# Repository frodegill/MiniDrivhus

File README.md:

## about project

Minidrivhus (english: indoor greenhouse) started as a dedicated system for pre-cultivating seeds indoors. It was based on ESP8266 and a custom shield that could support up to 3 soil sensors 3 water pumps and sensors for temperature, humidity and light intensity. There was also a relay for controlling an external grow light, and I've made custom PCBs for small and medium-sized indoor grow lights.  
With all this in place, I also started to make an outdoor greenhouse. When it was completed I expanded the project to also support outdoor greenhouse, which meant I had to add a relay to turn on and off a fan, sensors for outdoor temperature and humidity, a relay for operating a valve controlling water flow to an intermediate water reservoir, sensors for low and high level of water in this reservoir and voltage sensor for the solar panel charged 12V car battery that would power the whole system.  
Unfortunately, the first set of soil sensors did not handle humid/wet environment very well and the second (waterproof) soil sensor had a very limited value range, so I have now started redoing the whole system where the sensors are connected by RS-485 and the water pumps are controlled by a 16-channel multiplexer so one system can control up to 15 plants (having one channel act as an Off channel). To control this I needed more GPIO pins than the ESP8266 provided, so the new system will be based on an ESP32. Stay tuned for new and improved PCBs and source code!

## pictures

The original indoor greenhouse, ready for pre-cultivating seeds:  

Setup for the outdoor greenhouse. 3 systems, each controlling 3 water pumps, for a total of 9 buckets for plants. There is also a small controller for the main water valve and a solar charge controller  

I have 3 x 210 liter buckets for collecting rain water. The water is gravity-fed into an intermediate bucket in a corner of the greenhouse. All water pumps are located in this bucket. There are low- and high water level sensors that are used to control when a water valve is opened and water flows down from the 3 large buckets.  

A complete setup looks like this:  

..and after automatically watering plants all summer, it looks like this:

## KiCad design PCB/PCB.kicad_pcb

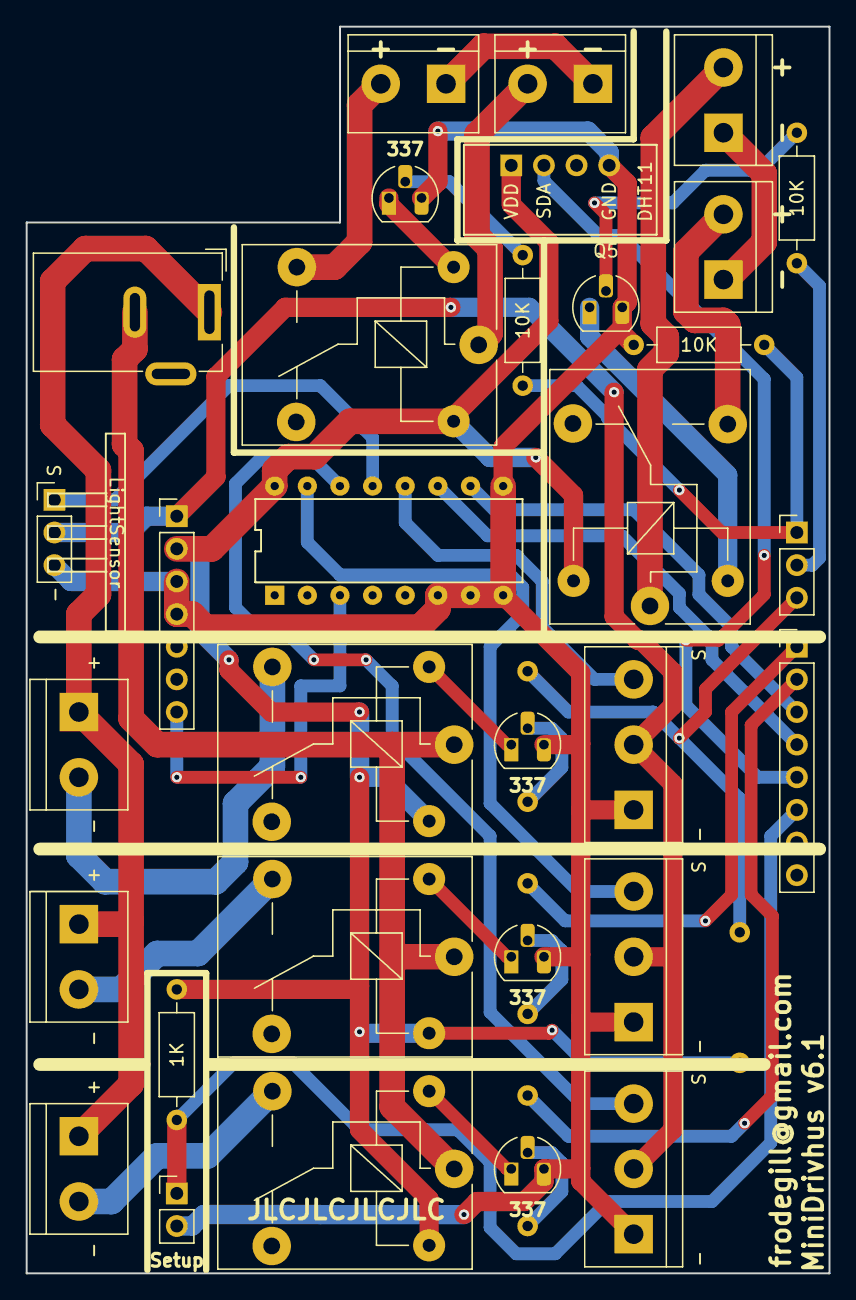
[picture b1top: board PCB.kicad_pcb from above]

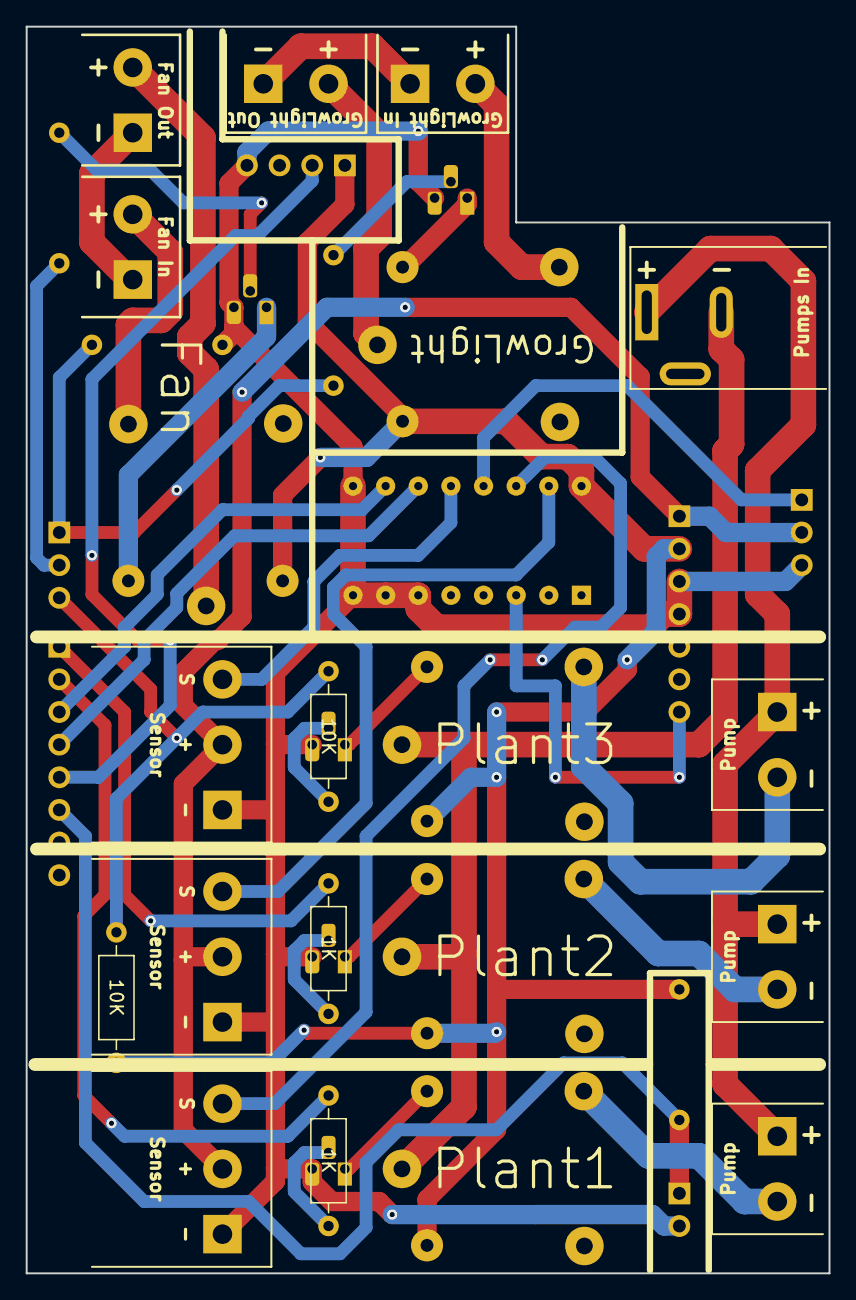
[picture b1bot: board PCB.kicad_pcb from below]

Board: 2 copper layers, 62.5 x 97.0 mm, 36 parts (4 on the bottom side), 38 nets.

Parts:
J1: PWR,A0; PinHeader_1x07_P2.54mm_Vertical
J2: Pump In; BarrelJack_Wuerth_6941xx301002
J3: LightSensor
J4: Pump1; TerminalBlock_bornier-2_P5.08mm
J5: Sensor1; TerminalBlock_bornier-3_P5.08mm
J6: GrowLight In; TerminalBlock_bornier-2_P5.08mm
J7: Pump2; TerminalBlock_bornier-2_P5.08mm
J8: Sensor2; TerminalBlock_bornier-3_P5.08mm
J9: Setup; PinHeader_1x02_P2.54mm_Vertical
J10: D8-D10; PinHeader_1x03_P2.54mm_Vertical
J11: D0-D7; PinHeader_1x08_P2.54mm_Vertical
J12: GrowLight Out; TerminalBlock_bornier-2_P5.08mm
J13: Pump3; TerminalBlock_bornier-2_P5.08mm
J14: Sensor3; TerminalBlock_bornier-3_P5.08mm
J15: Fan In; TerminalBlock_bornier-2_P5.08mm
J16: Fan Out; TerminalBlock_bornier-2_P5.08mm
K1: Relay1; Relay_SPDT_SANYOU_SRD_Series_Form_C
K2: RelayGrowlight; Relay_SPDT_SANYOU_SRD_Series_Form_C
K3: Relay2; Relay_SPDT_SANYOU_SRD_Series_Form_C
K4: Relay3; Relay_SPDT_SANYOU_SRD_Series_Form_C
K5: RelayFan; Relay_SPDT_SANYOU_SRD_Series_Form_C
Q1, Q2, Q3, Q4, Q5: BC337; TO-92_HandSolder
R1, R3, R4: 1K; R_Axial_DIN0207_L6.3mm_D2.5mm_P10.16mm_Horizontal
R2, R5, R6, R7, R8: 10K; R_Axial_DIN0207_L6.3mm_D2.5mm_P10.16mm_Horizontal
U1: DHT11; AM2302
U2: 74HC4051; 74HC4051N

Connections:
+3V3: J1.1, J3.2, J5.2, J8.2, J14.2
+5V: J1.2, K1.5, K2.5, K3.5, K4.5, K5.5, R4.1, R8.1, U1.1 (VCC), U2.16 (VCC)
GND: J1.3, J1.4, J3.3, J5.1, J8.1, J9.2, J14.1, Q1.3 (E), Q2.3 (E), Q3.3 (E), Q4.3 (E), Q5.3 (E), R7.1, U1.4 (GND), U2.6 (~E), U2.7 (VEE), U2.8 (GND), U2.9 (S2)
unnamed: J1.7, U2.3 (A)
unnamed: J2.2, K1.1, K3.1, K4.1
unnamed: J3.1, U2.13 (A0)
unnamed: J4.2, K1.3
unnamed: J5.3, U2.14 (A1)
unnamed: J6.2, K2.3
unnamed: J7.2, K3.3
unnamed: J8.3, U2.15 (A2)
unnamed: J10.1, R2.2, R7.2
unnamed: J10.2, R6.2
unnamed: J10.3, R5.2, R8.2
unnamed: J11.1, R3.2
unnamed: J11.2, R1.2
unnamed: J11.3, U2.10 (S1)
unnamed: J11.4, U2.11 (S0)
unnamed: J11.5, U1.2 (IO)
unnamed: J9.1, J11.6, R4.2
unnamed: J6.1, J12.1
unnamed: J12.2, K2.1
unnamed: J2.1, J4.1, J7.1, J13.1
unnamed: J13.2, K4.3
unnamed: J14.3, U2.12 (A3)
unnamed: J15.1, J16.1
unnamed: J15.2, K5.3
unnamed: J16.2, K5.1
unnamed: K1.2, Q1.1 (C)
unnamed: K2.2, Q2.1 (C)
unnamed: K3.2, Q3.1 (C)
unnamed: K4.2, Q4.1 (C)
unnamed: K5.2, Q5.1 (C)
unnamed: Q1.2 (B), R1.1
unnamed: Q2.2 (B), R2.1
unnamed: Q3.2 (B), R3.1
unnamed: Q4.2 (B), R5.1
unnamed: Q5.2 (B), R6.1

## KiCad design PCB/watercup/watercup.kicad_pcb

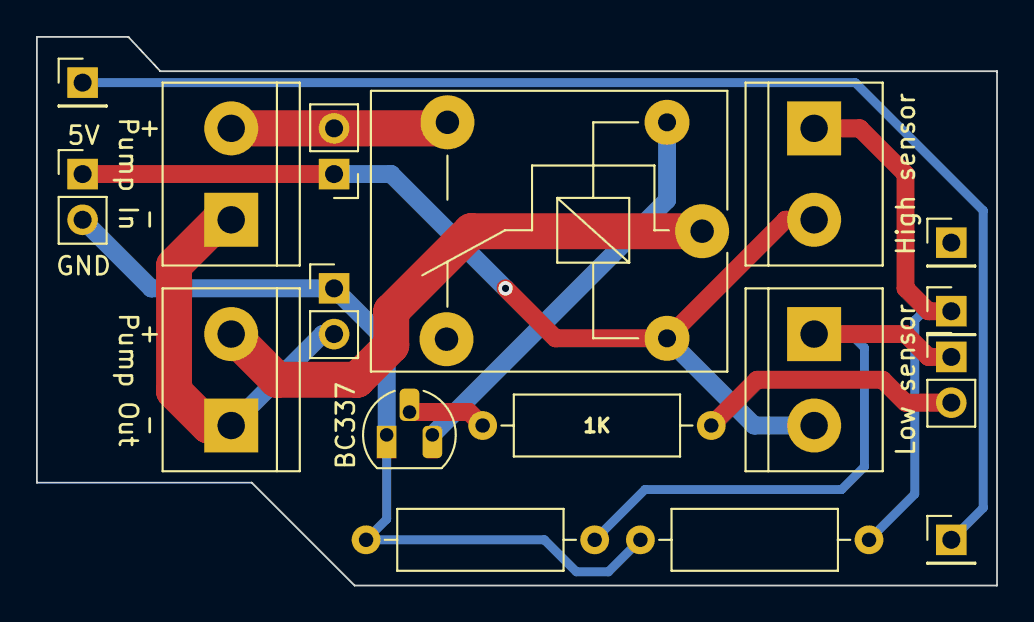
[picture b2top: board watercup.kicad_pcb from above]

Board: 2 copper layers, 53.3 x 30.5 mm, 17 parts (0 on the bottom side), 11 nets.

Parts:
J1, J4, J5, J6: Conn_01x02_Male; TerminalBlock_bornier-2_P5.08mm
J2, J7, J9, J10: Conn_01x02_Male; PinHeader_1x02_P2.54mm_Vertical
J3, J8, J11, J12: Conn_01x01_Male; PinHeader_1x01_P2.54mm_Vertical
K1: SANYOU_SRD_Form_C; Relay_SPDT_SANYOU_SRD_Series_Form_C
Q1: BC337; TO-92_HandSolder
R1, R2: 4K7; R_Axial_DIN0309_L9.0mm_D3.2mm_P12.70mm_Horizontal
R4: 1K; R_Axial_DIN0309_L9.0mm_D3.2mm_P12.70mm_Horizontal

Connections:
+5V: J2.1, J4.2, J5.2, J9.1, K1.5
GND: J2.2, J10.1, Q1.1 (C), R1.1, R2.1
unnamed: J1.1, J6.1, J10.2
unnamed: J1.2, K1.1
unnamed: J3.1, J5.1, R1.2
unnamed: J4.1, J7.1, R2.2
unnamed: J6.2, J9.2, K1.3
unnamed: J7.2, R4.1
unnamed: J11.1, J12.1
unnamed: K1.2, Q1.3 (E)
unnamed: Q1.2 (B), R4.2

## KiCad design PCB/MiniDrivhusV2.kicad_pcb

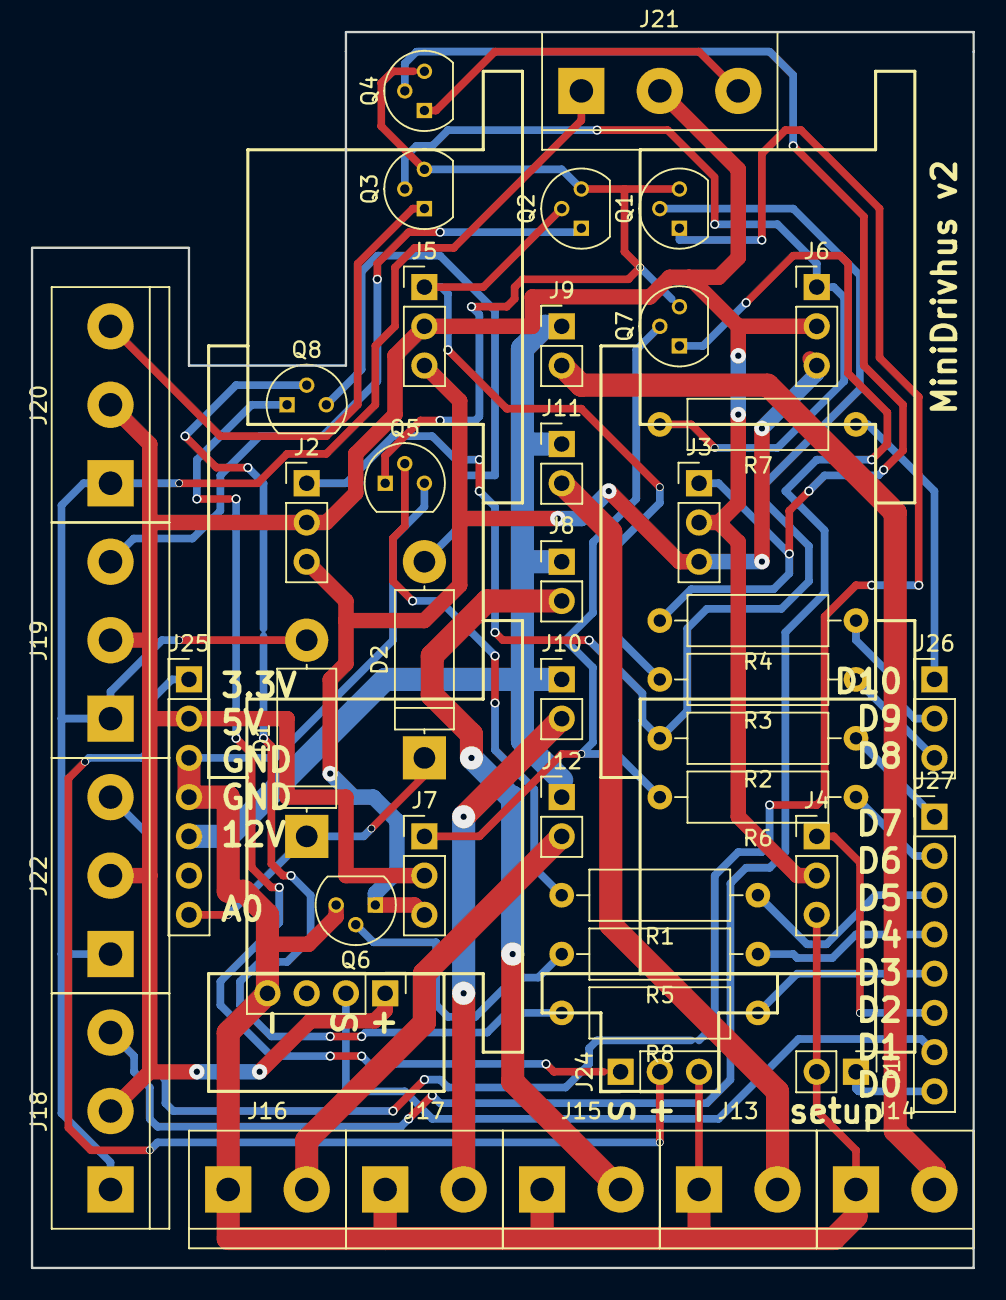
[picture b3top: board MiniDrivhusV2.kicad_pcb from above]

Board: 2 copper layers, 61.0 x 80.0 mm, 45 parts (0 on the bottom side), 39 nets.

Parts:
D1, D2: D; D_5W_P12.70mm_Horizontal
J1: SetupMode; Pin_Header_Straight_1x02_Pitch2.54mm
J2: Relay2; Pin_Header_Straight_1x03_Pitch2.54mm
J3: Relay5; Pin_Header_Straight_1x03_Pitch2.54mm
J4: RelayLight; Pin_Header_Straight_1x03_Pitch2.54mm
J5: Relay3; Pin_Header_Straight_1x03_Pitch2.54mm
J6: Relay4; Pin_Header_Straight_1x03_Pitch2.54mm
J7: Relay1; Pin_Header_Straight_1x03_Pitch2.54mm
J8: Conn3; Pin_Header_Straight_1x02_Pitch2.54mm
J9: Conn5; Pin_Header_Straight_1x02_Pitch2.54mm
J10: Conn2; Pin_Header_Straight_1x02_Pitch2.54mm
J11: Conn4; Pin_Header_Straight_1x02_Pitch2.54mm
J12: Conn1; Pin_Header_Straight_1x02_Pitch2.54mm
J13: Valve4; bornier2
J14: Valve5; bornier2
J15: Valve3; bornier2
J16: Valve1; bornier2
J17: Valve2; bornier2
J18: Sensor1; bornier3
J19: Sensor3; bornier3
J20: Sensor4; bornier3
J21: Sensor5; bornier3
J22: Sensor2; bornier3
J23: TempSensor; Pin_Header_Straight_1x04_Pitch2.54mm
J24: LightSensor; Pin_Header_Straight_1x03_Pitch2.54mm
J25: A0-Power-GND; Pin_Header_Straight_1x07_Pitch2.54mm
J26: D8-D10; Pin_Header_Straight_1x03_Pitch2.54mm
J27: D0-D7; Pin_Header_Straight_1x08_Pitch2.54mm
Q1: Select2; TO-92_Molded_Narrow
Q2: Select3; TO-92_Molded_Narrow
Q3: Select4; TO-92_Molded_Narrow
Q4: Select5; TO-92_Molded_Narrow
Q5: SensorMode; TO-92_Molded_Narrow
Q6: ValveMode; TO-92_Molded_Narrow
Q7: Select1; TO-92_Molded_Narrow
Q8: LightMode; TO-92_Molded_Narrow
R1, R5, R8: R; R_Axial_DIN0309_L9.0mm_D3.2mm_P12.70mm_Horizontal
R2: R2; R_Axial_DIN0309_L9.0mm_D3.2mm_P12.70mm_Horizontal
R3: R3; R_Axial_DIN0309_L9.0mm_D3.2mm_P12.70mm_Horizontal
R4: R5; R_Axial_DIN0309_L9.0mm_D3.2mm_P12.70mm_Horizontal
R6: R1; R_Axial_DIN0309_L9.0mm_D3.2mm_P12.70mm_Horizontal
R7: R4; R_Axial_DIN0309_L9.0mm_D3.2mm_P12.70mm_Horizontal

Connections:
unnamed: D1.1, D2.1, J25.7
unnamed: D1.2, J18.1, J19.1, J20.1, J21.1, J22.1
unnamed: D2.2, Q8.3
unnamed: J1.1, J27.8
unnamed: J1.2, J4.3, J13.1, J14.1, J15.1, J16.1, J17.1, J23.4, J24.3, J25.3, J25.4, Q5.3, Q6.3
unnamed: J2.1, Q1.2, R2.2
unnamed: J2.3, J3.3, J5.3, J6.3, J7.3, Q6.1
unnamed: J3.1, Q4.2, R4.2
unnamed: J5.1, Q2.2, R3.2
unnamed: J6.1, Q3.2, R7.2
unnamed: J7.1, Q7.2, R6.2
unnamed: J8.1, J9.1, J10.1, J11.1, J12.1, J25.5
unnamed: J10.2, J17.2
unnamed: J11.2, J13.2
unnamed: J12.2, J16.2
unnamed: J9.2, J14.2
unnamed: J8.2, J15.2
unnamed: J2.2, J3.2, J4.2, J5.2, J6.2, J7.2, J18.2, J19.2, J20.2, J21.2, J22.2, J23.1, J25.2
unnamed: J18.3, Q7.1
unnamed: J19.3, Q2.1
unnamed: J20.3, Q3.1
unnamed: J21.3, Q4.1
unnamed: J22.3, Q1.1
unnamed: J23.2, J27.7
unnamed: J24.1, Q8.1
unnamed: J24.2, J25.1
unnamed: J26.1, R7.1
unnamed: J26.2, R4.1
unnamed: J26.3, R3.1
unnamed: J27.1, R2.1
unnamed: J27.2, R6.1
unnamed: J27.3, R1.1
unnamed: J27.4, R5.1
unnamed: J27.5, R8.1
unnamed: J4.1, J27.6
unnamed: Q1.3, Q2.3, Q3.3, Q4.3, Q5.1, Q7.3
unnamed: Q5.2, R1.2
unnamed: Q6.2, R5.2
unnamed: Q8.2, R8.2

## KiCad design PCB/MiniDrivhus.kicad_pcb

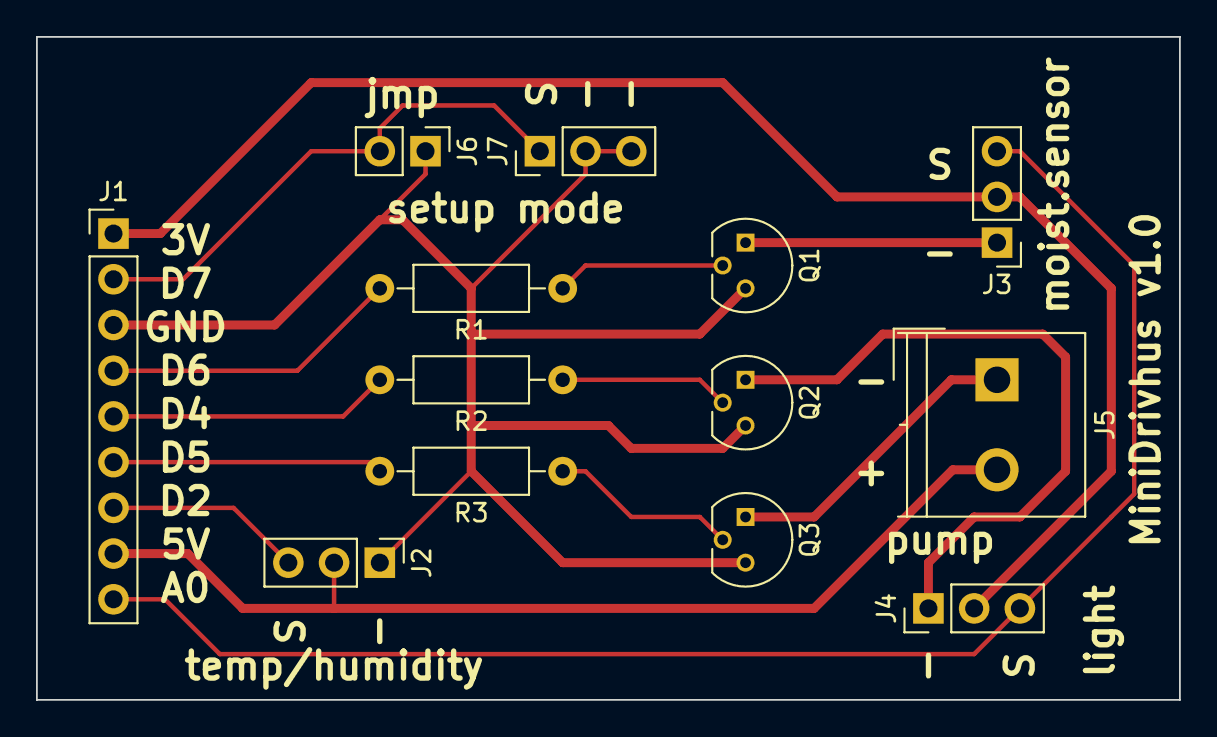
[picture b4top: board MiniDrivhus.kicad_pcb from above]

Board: 2 copper layers, 63.5 x 36.8 mm, 13 parts (0 on the bottom side), 15 nets.

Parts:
J1: Arduino; Pin_Header_Straight_1x09_Pitch2.54mm
J2: Temp/Humidity; Pin_Header_Straight_1x03_Pitch2.54mm
J3: Moist.Sensor; Pin_Header_Straight_1x03_Pitch2.54mm
J4: Light Sensor; Pin_Header_Straight_1x03_Pitch2.54mm
J5: Pump; TerminalBlock_Philmore_TB132_02x5mm_Straight
J6: SetupJmp; Pin_Header_Straight_1x02_Pitch2.54mm
J7: SetupSwitch; Pin_Header_Straight_1x03_Pitch2.54mm
Q1, Q2, Q3: BC337; TO-92_Molded_Narrow_Reverse
R1, R2, R3: R; R_Axial_DIN0207_L6.3mm_D2.5mm_P10.16mm_Horizontal

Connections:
unnamed: J1.1, J3.2, J4.2
unnamed: J1.2, J6.2, J7.1
unnamed: J1.3, J2.1, J6.1, J7.2, J7.3, Q1.3, Q2.3, Q3.3
unnamed: J1.4, R1.2
unnamed: J1.5, R2.2
unnamed: J1.6, R3.2
unnamed: J1.7, J2.3
unnamed: J1.8, J2.2, J5.2
unnamed: J1.9, J3.3, J4.3
unnamed: J3.1, Q1.1
unnamed: J4.1, Q2.1
unnamed: J5.1, Q3.1
unnamed: Q1.2, R1.1
unnamed: Q2.2, R2.1
unnamed: Q3.2, R3.1

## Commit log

2018-03-24 My SSID pwd is public, but not needed in source code
2018-03-25 Invert water-value. 0.0 is dry, 100.0 is wet
2018-03-27 Added fritzing
2018-03-30 Minor adjustment of trigger values, and started working on setup mode
2018-04-01 Added KiCad PCB
2018-04-02 Added setup-mode (pull D7 to GND before boot), including some really ugly string parsing
2019-01-05 Prepare for new PCB, adding mqtt support
2019-01-11 More complete MQTT support
2019-01-25 Quite a few bug-fixes and features...
2019-01-26 Fixed password persist and MQTT values for temp/humidity
2019-01-26 Light worked on first attempt. Use actual (and correct) value :-)
2019-02-23 New and improved PCB
2019-04-18 Added lots of debug messages
2019-04-25 Adapted for WeMos D1 R32 board
2019-05-11 PCB for the Wemos D1 R32
2019-05-11 Implemented valve grace period, and made ESP32 network handling more robust
2020-02-02 Preparing for MiniDrivhus v4
2020-02-13 Some renaming. Completed mqtt updates and fixed some code smell
2020-03-29 Some cleanup
2020-04-10 Moisture values are now percent, fixed mqtt subscribe topics typo and cleaned up debug message calls
2020-04-10 Added topic to request instant watering
2020-04-20 Kicad-files for MivinDrivhus_v5
2020-04-30 PCB v5.1
2020-04-30 Added support for 3 plants
2020-05-16 Renamed Debug to Log
2021-02-27 Added NTP and support for controlling growlight
2021-02-27 Minor log adjustments
2022-04-11 Misc fixes that has started collecting dust locally
2022-04-13 Added support for the fan relay
2022-04-13 Added ino for the watercup arduino controller
2022-04-13 Added watercup controller PCB files
2022-06-19 Added MQTT support to watercup
2022-06-19 Added fan support to minidrivhus
2022-06-19 Added config script
2022-07-17 Added support for stepper motor
2022-08-02 Possible to enable plants individually
2023-03-11 Do not start grace period at startup
2023-03-11 Process all pending MQTT messages in the MQTT loop
2023-05-06 Don't use a hard limit for turning fan on/off
2023-09-28 Added some photos
